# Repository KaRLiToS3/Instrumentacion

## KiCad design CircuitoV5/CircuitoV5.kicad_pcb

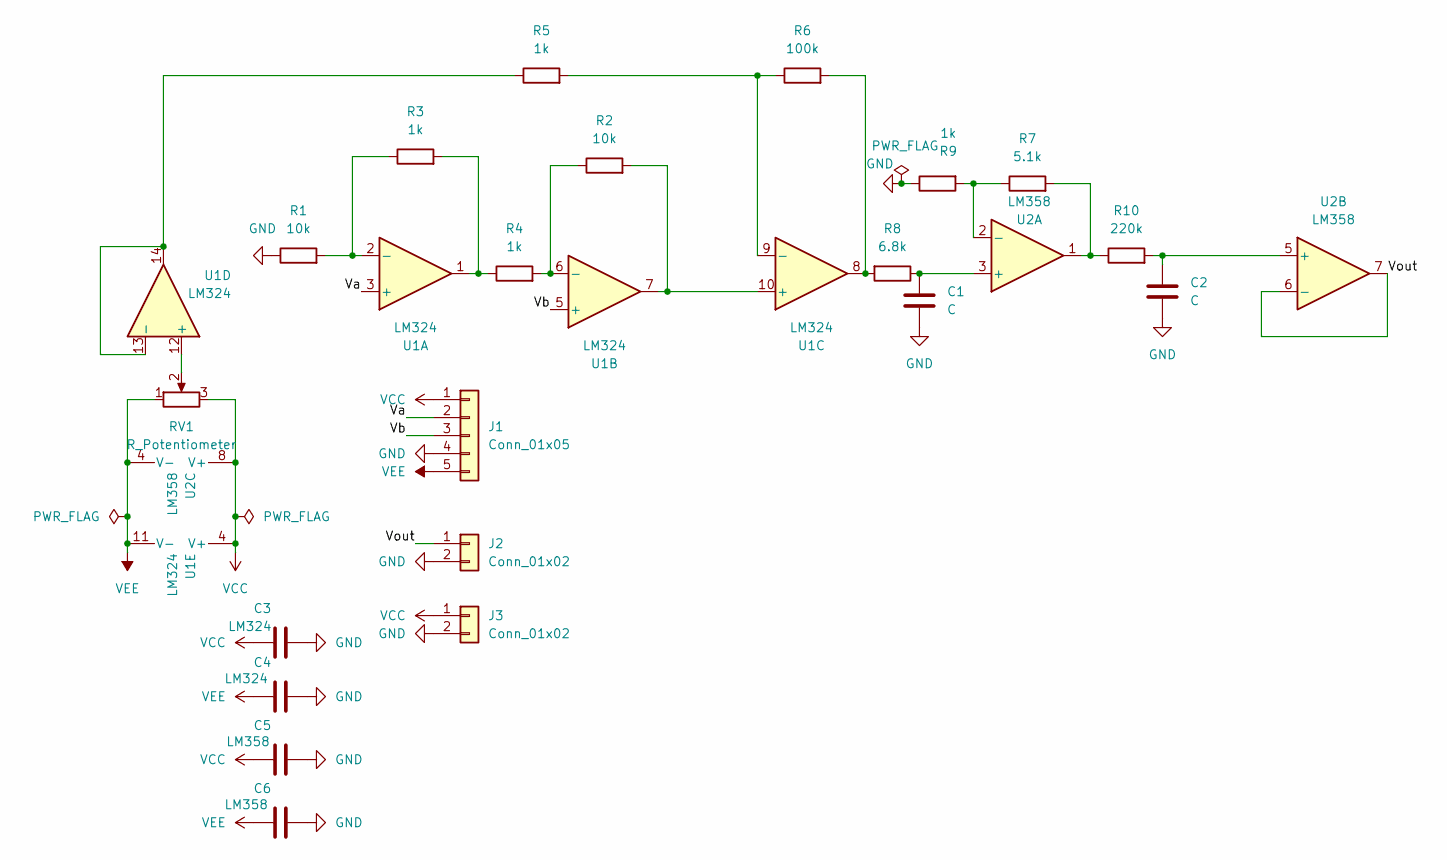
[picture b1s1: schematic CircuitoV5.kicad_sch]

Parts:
C1, C2: C; C_Rect_L9.5mm_W4.5mm_P5.00mm_MKT
C3, C4: LM324; C_Disc_D5.0mm_W2.5mm_P2.50mm
C5, C6: LM358; C_Disc_D5.0mm_W2.5mm_P2.50mm
J1: Conn_01x05; PinSocket_1x05_P2.54mm_Horizontal
J2, J3: Conn_01x02; PinSocket_1x02_P2.54mm_Vertical
R1, R2: 10k; R_Axial_DIN0207_L6.3mm_D2.5mm_P10.16mm_Horizontal; LCSC_Id C2906861
R3, R4, R5, R9: 1k; R_Axial_DIN0207_L6.3mm_D2.5mm_P10.16mm_Horizontal; LCSC_Id C21190
R6: 100k; R_Axial_DIN0207_L6.3mm_D2.5mm_P10.16mm_Horizontal; LCSC_Id C2906980
R7: 5.1k; R_Axial_DIN0207_L6.3mm_D2.5mm_P10.16mm_Horizontal; LCSC_Id C2906874
R8: 6.8k; R_Axial_DIN0207_L6.3mm_D2.5mm_P10.16mm_Horizontal; LCSC_Id C114632
R10: 220k; R_Axial_DIN0207_L6.3mm_D2.5mm_P10.16mm_Horizontal; LCSC_Id C2907013
RV1: R_Potentiometer; Potentiometer_Bourns_3296W_Vertical; LCSC_Id C48997937
U1: LM324; DIP-14_W7.62mm; LCSC_Id C71035
U2: LM358; DIP-8_W7.62mm; LCSC_Id C5213

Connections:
/Va: J1.2, U1.3 (+)
/Vb: J1.3, U1.5 (+)
/Vout: J2.1, U2.6 (-), U2.7
GND: C1.2, C2.2, C3.2, C4.2, C5.2, C6.2, J1.4, J2.2, J3.2, R1.1, R9.1
unnamed: R3.2, R4.1, U1.1
unnamed: R6.2, R8.2, U1.8
unnamed: R7.2, R10.1, U2.1
unnamed: R1.2, R3.1, U1.2 (-)
unnamed: R2.1, R4.2, U1.6 (-)
unnamed: R2.2, U1.7, U1.10 (+)
unnamed: R5.2, R6.1, U1.9 (-)
unnamed: RV1.2, U1.12 (+)
unnamed: R5.1, U1.13 (-), U1.14
unnamed: C1.1, R8.1, U2.3 (+)
unnamed: R7.1, R9.2, U2.2 (-)
unnamed: C2.1, R10.2, U2.5 (+)
VCC: C3.1, C5.1, J1.1, J3.1, RV1.3, U1.4 (V+), U2.8 (V+)
VEE: C4.1, C6.1, J1.5, RV1.1, U1.11 (V-), U2.4 (V-)

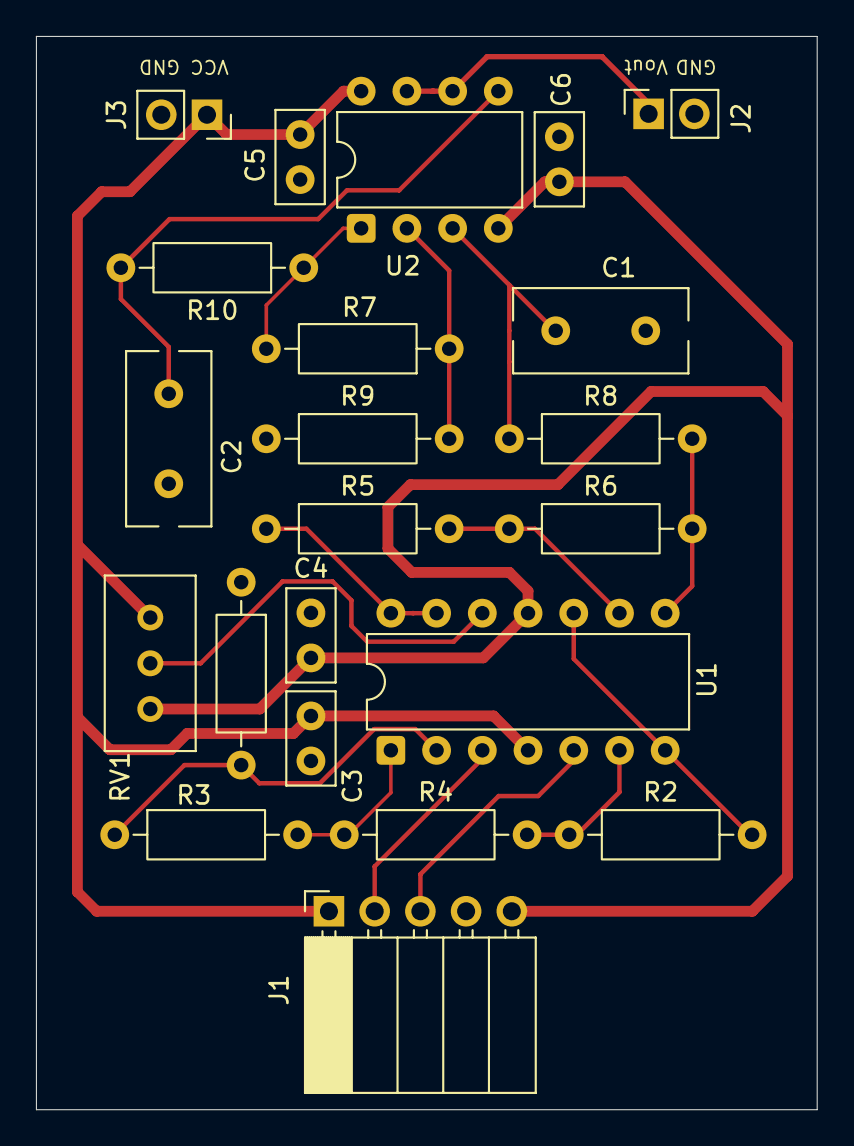
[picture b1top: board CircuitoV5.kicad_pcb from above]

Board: 2 copper layers, 43.4 x 59.6 mm, 22 parts (0 on the bottom side), 18 nets.

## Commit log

2026-04-02 Schematic hecha, enrutado V1 planteado y empezado
2026-04-02 Enrutamiento v2 parcial
2026-04-02 Enrutado completo V3 y errores importantes corregidos, quedan algunos por ignorar
2026-04-04 Ultimos retoques de enrutamiento
2026-04-15 componentes añadidos y proyecto ligeramente reordenado
2026-04-18 Routed and done
2026-04-22 Añadidos tag en silkscreen para pines de conexion
2026-04-24 Ultimas actualizaciones y correcciones
